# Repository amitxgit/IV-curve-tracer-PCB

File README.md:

# USB-Controlled SCPI I-V Curve Tracer

A self-built, PCB-based bench instrument that sweeps voltage across a
device under test (DUT) — diode, BJT, MOSFET, resistor — and measures
the resulting current, streaming SCPI-style commands over USB-CDC to a
Python client that plots and logs the I-V curve.

Think of it as a single-channel, low-cost analogue of a lab SMU
(Keithley 2635B / Keysight B2985B class instrument), built from scratch
to demonstrate instrumentation design: precision analogue signal
chain, embedded firmware, a real command protocol, and a PC-side
automation client.

## Repository layout

```
iv-curve-tracer/
├── hardware/           KiCad project + schematic/connection notes
├── firmware/           STM32F103 firmware (SCPI parser, drivers, sweep engine)
├── software/           Python PC client (iv_tracer package)
├── docs/               BOM, pin mapping, SCPI reference, PCB layout rules, validation plan
├── LICENSE-HARDWARE    CERN-OHL-P-2.0 (hardware design files)
└── LICENSE-SOFTWARE    MIT (firmware + PC client)
```

## Hardware

The carrier board takes a Blue Pill, two MCP4725 DAC breakouts and an
INA219 breakout on sockets, and adds the op-amp buffer / gain stage,
the current-limit resistor, the Kelvin V-sense divider and the DUT
terminal. KiCad project: `hardware/kicad/iv-curve-tracer-pcb/`.
Schematic PDF: `docs/schematic.pdf`. Build notes, jumper settings and
module pin order: `hardware/schematic_notes.md`.

| Top | Bottom |
|-----|--------|
|  |  |

## Quick start (once hardware is built)

```bash
cd software
pip install -r requirements.txt
python -m iv_tracer.cli --port /dev/ttyACM0 --start 0 --stop 5 --step 0.05 --dwell 10 --plot --save diode_sweep.csv
```

## Project status

- [x] Schematic captured in KiCad (ERC clean)
- [x] PCB laid out, 2-layer carrier board rev 1.0 (DRC clean)
- [ ] PCB fabricated (JLCPCB, 2-layer)
- [ ] Firmware: DAC sweep + USB-CDC bring-up (drivers + SCPI parser + sweep engine written; needs on-board bring-up)
- [x] Firmware: SCPI parser + sweep engine (with error queue + *RST state reset)
- [x] Python client: sweep/plot/CSV export
- [x] Hardware-free simulator + pytest suite (run the full pipeline before the board exists)
- [ ] Validation: known diode + known resistor vs datasheet/multimeter (on real hardware)

## Why this exists

Built as a standalone portfolio project for semiconductor test /
applications engineering roles — demonstrates the same instrumentation
skill set (PyVISA/SCPI automation, precision analogue measurement)
used in real lab work, but from the instrument-design side rather than
the instrument-user side.

See `docs/validation_plan.md` for how the tracer is validated against
known references, and `docs/scpi_command_reference.md` for the full
command set.

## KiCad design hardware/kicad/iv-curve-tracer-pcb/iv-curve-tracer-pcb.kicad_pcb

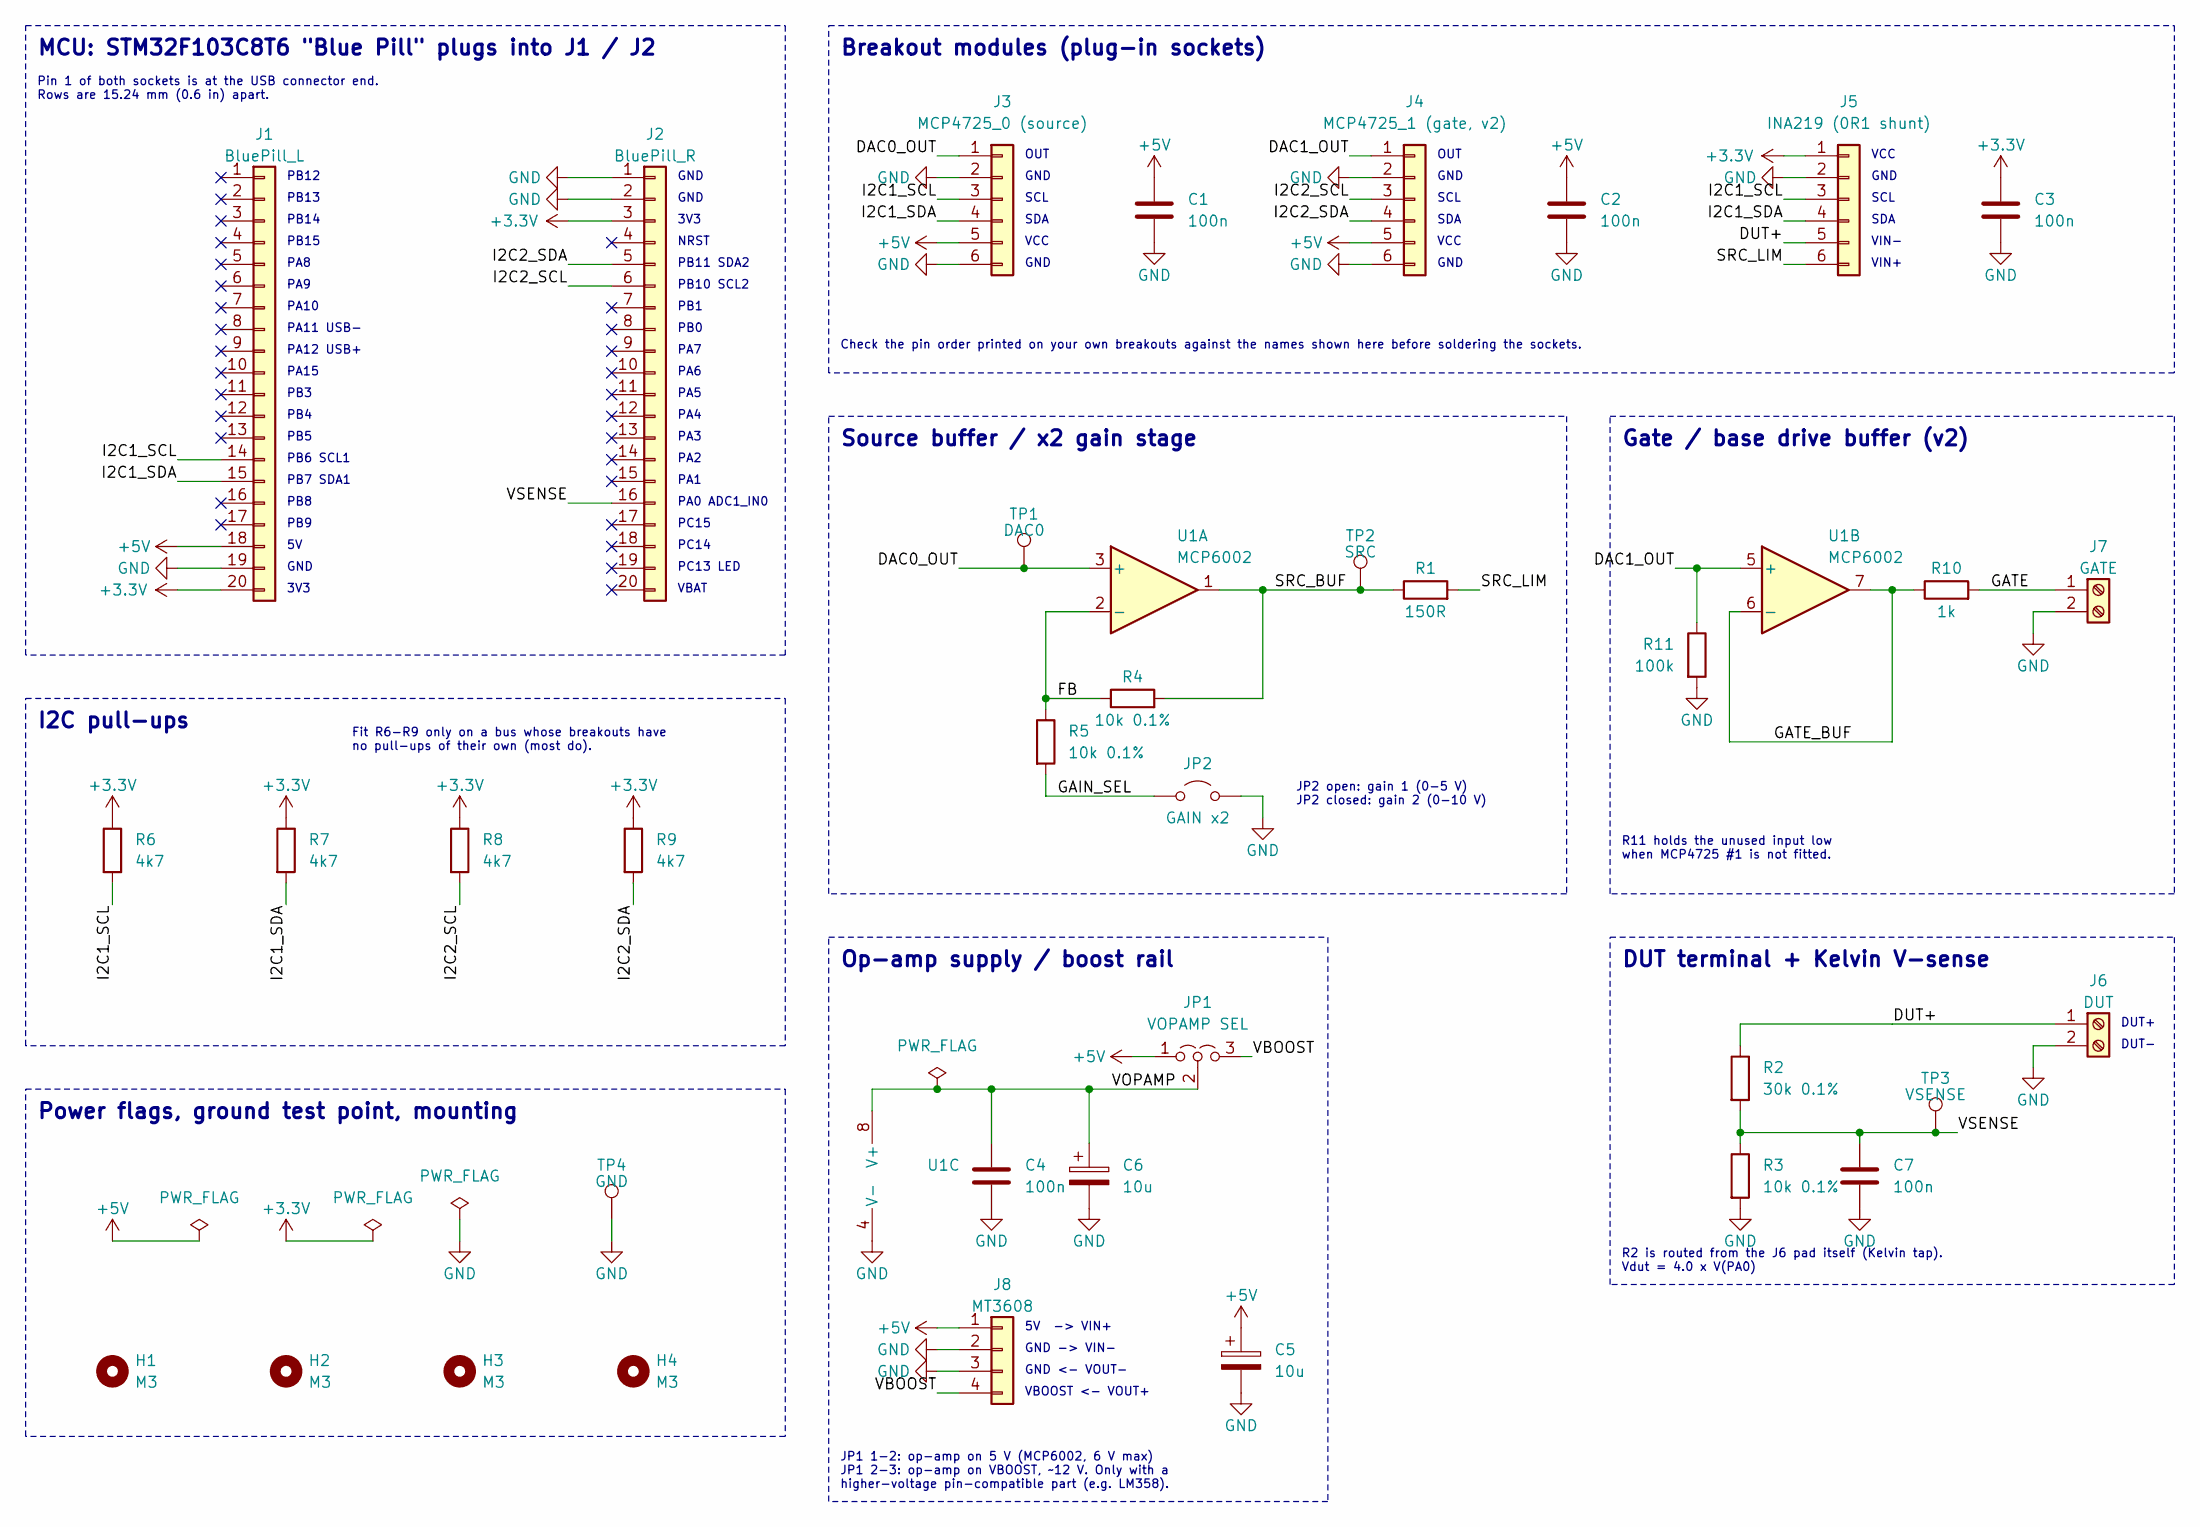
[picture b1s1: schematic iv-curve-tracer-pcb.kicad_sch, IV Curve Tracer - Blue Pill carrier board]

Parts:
C1, C2, C3, C4, C7: 100n; C_Disc_D5.0mm_W2.5mm_P5.00mm
C5, C6: 10u; CP_Radial_D5.0mm_P2.00mm
H1, H2, H3, H4: M3; MountingHole_3.2mm_M3
J1: BluePill_L; PinSocket_1x20_P2.54mm_Vertical
J2: BluePill_R; PinSocket_1x20_P2.54mm_Vertical
J3: MCP4725_0 (source); PinSocket_1x06_P2.54mm_Vertical
J4: MCP4725_1 (gate, v2); PinSocket_1x06_P2.54mm_Vertical
J5: INA219 (0R1 shunt); PinSocket_1x06_P2.54mm_Vertical
J6: DUT; TerminalBlock_Phoenix_MKDS-1,5-2_1x02_P5.00mm_Horizontal
J7: GATE; TerminalBlock_Phoenix_MKDS-1,5-2_1x02_P5.00mm_Horizontal
J8: MT3608; PinHeader_1x04_P2.54mm_Vertical
JP1: VOPAMP SEL; PinHeader_1x03_P2.54mm_Vertical
JP2: GAIN x2; PinHeader_1x02_P2.54mm_Vertical
R1: 150R; R_Axial_DIN0207_L6.3mm_D2.5mm_P10.16mm_Horizontal
R2: 30k 0.1%; R_Axial_DIN0207_L6.3mm_D2.5mm_P10.16mm_Horizontal
R3, R4, R5: 10k 0.1%; R_Axial_DIN0207_L6.3mm_D2.5mm_P10.16mm_Horizontal
R6, R7, R8, R9: 4k7; R_Axial_DIN0207_L6.3mm_D2.5mm_P10.16mm_Horizontal
R10: 1k; R_Axial_DIN0207_L6.3mm_D2.5mm_P10.16mm_Horizontal
R11: 100k; R_Axial_DIN0207_L6.3mm_D2.5mm_P10.16mm_Horizontal
TP1: DAC0; TestPoint_THTPad_D2.0mm_Drill1.0mm
TP2: SRC; TestPoint_THTPad_D2.0mm_Drill1.0mm
TP3: VSENSE; TestPoint_THTPad_D2.0mm_Drill1.0mm
TP4: GND; TestPoint_THTPad_D2.0mm_Drill1.0mm
U1: MCP6002; DIP-8_W7.62mm_Socket

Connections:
+3.3V: C3.1, J1.20, J2.3, J5.1, R6.1, R7.1, R8.1, R9.1
+5V: C1.1, C2.1, C5.1, J1.18, J3.5, J4.5, J8.1, JP1.1 (A)
/DAC0_OUT: J3.1, TP1.1, U1.3 (+)
/DAC1_OUT: J4.1, R11.1, U1.5 (+)
/DUT+: J5.5, J6.1, R2.1
/FB: R4.1, R5.1, U1.2 (-)
/GAIN_SEL: JP2.1 (A), R5.2
/GATE: J7.1, R10.2
/GATE_BUF: R10.1, U1.6 (-), U1.7
/I2C1_SCL: J1.14, J3.3, J5.3, R6.2
/I2C1_SDA: J1.15, J3.4, J5.4, R7.2
/I2C2_SCL: J2.6, J4.3, R8.2
/I2C2_SDA: J2.5, J4.4, R9.2
/SRC_BUF: R1.1, R4.2, TP2.1, U1.1
/SRC_LIM: J5.6, R1.2
/VBOOST: J8.4, JP1.3 (B)
/VOPAMP: C4.1, C6.1, JP1.2 (C), U1.8 (V+)
/VSENSE: C7.1, J2.16, R2.2, R3.1, TP3.1
GND: C1.2, C2.2, C3.2, C4.2, C5.2, C6.2, C7.2, J1.19, J2.1, J2.2, J3.2, J3.6, J4.2, J4.6, J5.2, J6.2, J7.2, J8.2, J8.3, JP2.2 (B), R3.2, R11.2, TP4.1, U1.4 (V-)

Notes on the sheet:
VBAT
PB4
PB1
VIN+
PB0
PB7 SDA1
Pin 1 of both sockets is at the USB connector end. Rows are 15.24 mm (0.6 in) apart.
GND
PB6 SCL1
R2 is routed from the J6 pad itself (Kelvin tap). Vdut = 4.0 x V(PA0)
PA5
PA9
NRST
PB3
VBOOST <- VOUT+
PA0 ADC1_IN0
DUT terminal + Kelvin V-sense
PA12 USB+
SDA
DUT-
Breakout modules (plug-in sockets)
VIN-
PC14
PB8
3V3
SCL
PB15
Source buffer / x2 gain stage
PB14
DUT+
VCC
PA3
PA1
PC13 LED
GND <- VOUT-
PB10 SCL2
PB11 SDA2
Gate / base drive buffer (v2)
PB9
PA4

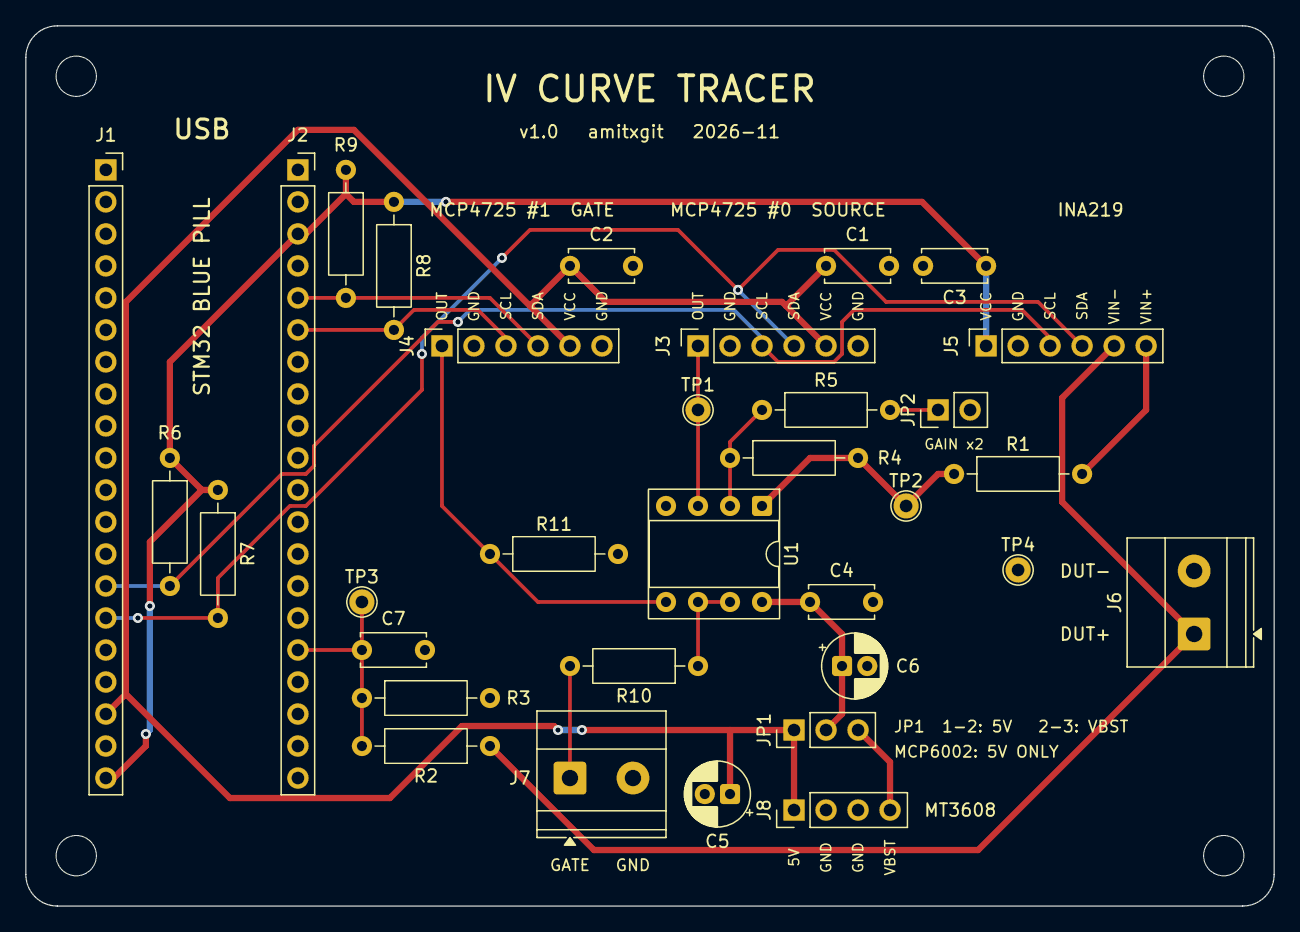
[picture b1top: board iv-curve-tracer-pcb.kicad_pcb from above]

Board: 2 copper layers, 99.1 x 69.8 mm, 37 parts (0 on the bottom side), 19 nets.
